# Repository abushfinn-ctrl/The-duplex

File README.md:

# The-duplex
A wireless split keyboard with 42 keys, made in a 3d printed case. Designed and built for HackClub and improved typing erogonomics. I got a new Macbook lately and my old keyboard was on it's last few breaths, so I decided to make a new keyboard that is also ergonomic. You can use the PCB files to order the PCB from Jlcpcb or your preffered PCB manufacturer. The bill of materials is also provided, look at aliexpress but if the parts are available locally for cheaper then obviously that would work aswell. I printed the case in Clay colour Matte PLA with a layer height of 0.2mm on my Prusa Mk3s+.
# Finished!
I finished the project and i've been waiting to be a little bit more free with school to do this journal. I modified the case because it was going to be too thick with the battery inside so I decided to put the battery on top next to the keys. Everything went pretty smoothly I used some heat inserts and double sided tape for the battery. Overall I like it, it looks cool but I'm not sure I really enjoy typing on it. It's not quite the right positions for the keys and it's just off so I can only get 45WPM vs my normal 110WPM. But i learnt a lot and had fun! I added some leather on the bottom so it grips a little better too.

# The Schematic
The schematic is split into a left and right side with the root sheet having the mousebites.
Here is the left side. 

And here is the right side. Exactly the same.

 We can achieve this by using hierarchical sheets. 
 
To make hierarchical sheeting you can click this button on the side bar or the keyboard button S.
Once setup your heirarchy should look like this.

# The PCB
The PCB is fairly simple. Import a template into kicad to use as a layout tool on where to place the switches. I used ergogen (https://ergogen.xyz/new) to edit a layout and then important that into Kicad as an image to get roughly lined up. Here is my PCB at the very end after routing and drawing my edge cuts.

Don't forget to add some customisation like your name!

# The Case 
I designed the case in Autodesk Fusion, there we're 100% some issues but nothing a bit of time and youtube videos can't fix. I designed the top and then bottom then mirrored and copied them for the other side.

# BOM
| Item                        | Description                                  | Quantity | Unit Price (CAD$) | Total Price (CAD$) | Unit Price (USD$) | Total Price (USD$) | URL                                                                                                                                                                                                                                                                                                                                                                                                                                                                                                                                                                                                                                                                                                       | Running total (CAD$ with tax) | Running total (USD$ with tax) |
| --------------------------- | -------------------------------------------- | -------- | ----------------- | ------------------ | ----------------- | ------------------ | --------------------------------------------------------------------------------------------------------------------------------------------------------------------------------------------------------------------------------------------------------------------------------------------------------------------------------------------------------------------------------------------------------------------------------------------------------------------------------------------------------------------------------------------------------------------------------------------------------------------------------------------------------------------------------------------------------- | ----------------------------- | ----------------------------- |
| 102050 1000mAh LiPO Battery | 20mm\*50mm\*10mm 3.7v Lithium battery. 2Pack | 1        | $12.38            | $12.38             | $8.90             | $8.90              | [Battery](https://www.aliexpress.com/item/1005006394926759.html?spm=a2g0o.cart.0.0.717138da7HBbtz&mp=1&pdp_npi=6%40dis%21CAD%21CAD%2020.30%21CAD%2012.38%21%21CAD%2012.38%21%21%21%4021030a6217721181818113051eb8cd%2112000037011657000%21ct%21CA%21-1%21%211%210%21)                                                                                                                                                                                                                                                                                                                                                                                                                                     | 12.38$                        | 8.90$                         |
| Gateron Switches 50 Pack    | 50 Gateron Auburn Switches                   | 1        | $22.71            | $22.71             | $16.33            | $16.33             | [Switches](https://www.aliexpress.com/item/1005006091988869.html?spm=a2g0o.cart.0.0.717138daN9Xo9a&mp=1&pdp_npi=6%40dis%21CAD%21CAD%2022.71%21CAD%2016.50%21%21CAD%2016.50%21%21%21%402103126e17721187661706203ef36d%2112000035698597741%21ct%21CA%21-1%21%211%210%21)                                                                                                                                                                                                                                                                                                                                                                                                                                    | 35.09$                        | 25.23$                        |
| XIAO nRF52840               | XIAO 2 pack microcontroller                  | 1        | $47.72            | $47.72             | $34.31            | $34.31             | [XIAO](https://www.aliexpress.com/item/1005009937098547.html?spm=a2g0o.cart.0.0.717138daN9Xo9a&mp=1&pdp_npi=6%40dis%21CAD%21CAD%2038.79%21CAD%2038.79%21%21CAD%2038.79%21%21%21%402103126e17721187661706203ef36d%2112000053206770722%21ct%21CA%21-1%21%211%210%21)                                                                                                                                                                                                                                                                                                                                                                                                                                        | 82.81$                        | 59.54$                        |
| Gateron Hotswap Sockets     | 70pack of Gateron hotswap sockets            | 1        | $22.64            | $22.64             | $16.28            | $16.28             | [Hotswap Sockets](https://www.aliexpress.com/item/1005007267551458.html?spm=a2g0o.productlist.main.2.6775445alZJMq9&algo_pvid=8333edd5-5946-4213-8dd2-250f714a57a7&algo_exp_id=8333edd5-5946-4213-8dd2-250f714a57a7-1&pdp_ext_f=%7B%22order%22%3A%22116%22%2C%22eval%22%3A%221%22%2C%22fromPage%22%3A%22search%22%7D&pdp_npi=6%40dis%21CAD%2111.03%211.59%21%21%2153.99%217.80%21%402101d6ff17721194373734938ee5ee%2112000040367341585%21sea%21CA%210%21ABX%211%210%21n_tag%3A-29910%3Bd%3Af7fad9c5%3Bm03_new_user%3A-29895%3BpisId%3A5000000197831975&curPageLogUid=QSxKiYfJkGM5&utparam-url=scene%3Asearch%7Cquery_from%3A%7Cx_object_id%3A1005007267551458%7C_p_origin_prod%3A)                        | 105.45$                       | 75.81$                        |
| PCB                         | 5 PCB's ordered from JLCPCB                  | 1        | $58.41            | $58.41             | $41.99            | $41.99             | N/A                                                                                                                                                                                                                                                                                                                                                                                                                                                                                                                                                                                                                                                                                                       | 163.86$                       | 117.81$                       |
| 1N5189 Diodes               | 100 pieces                                   | 1        | $3.05             | $3.05              | $2.19             | $2.19              | [DIODE](https://www.aliexpress.com/item/1005004617332808.html?spm=a2g0o.productlist.main.2.6d095c7c8zgvdj&algo_pvid=a741c6a4-8f37-4fc7-9e49-6e10b294d7f1&algo_exp_id=a741c6a4-8f37-4fc7-9e49-6e10b294d7f1-1&pdp_ext_f=%7B%22order%22%3A%2227%22%2C%22spu_best_type%22%3A%22price%22%2C%22eval%22%3A%221%22%2C%22fromPage%22%3A%22search%22%7D&pdp_npi=6%40dis%21CAD%213.05%211.59%21%21%212.19%211.14%21%402101e2b417736070752314599edabc%2112000029848432899%21sea%21CA%210%21ABX%211%210%21n_tag%3A-29910%3Bd%3A893a898a%3Bm03_new_user%3A-29895%3BpisId%3A5000000197831859&curPageLogUid=KM5DeZYwbAHX&utparam-url=scene%3Asearch%7Cquery_from%3A%7Cx_object_id%3A1005004617332808%7C_p_origin_prod%3A) | 166.91$                       | 120.00$                       |
| Keycaps                     | Already have                                 |          |                   |                    |                   |                    |                                                                                                                                                                                                                                                                                                                                                                                                                                                                                                                                                                                                                                                                                                           |                               |                               |

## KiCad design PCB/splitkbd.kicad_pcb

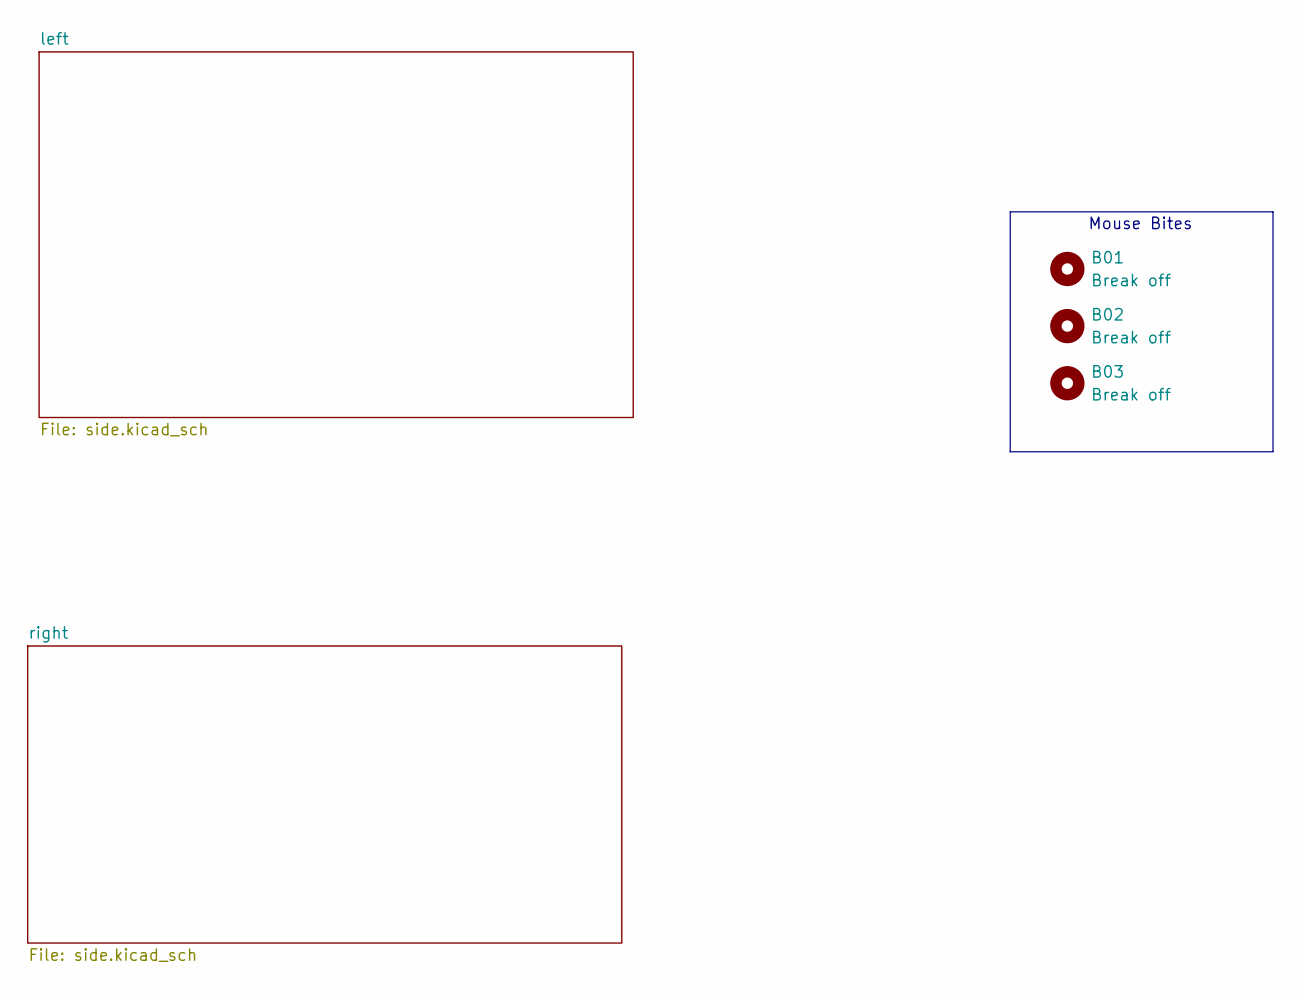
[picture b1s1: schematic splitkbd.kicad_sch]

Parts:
B01, B02, B03: Break off; mouse-bite-5mm-slot

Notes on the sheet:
Mouse Bites

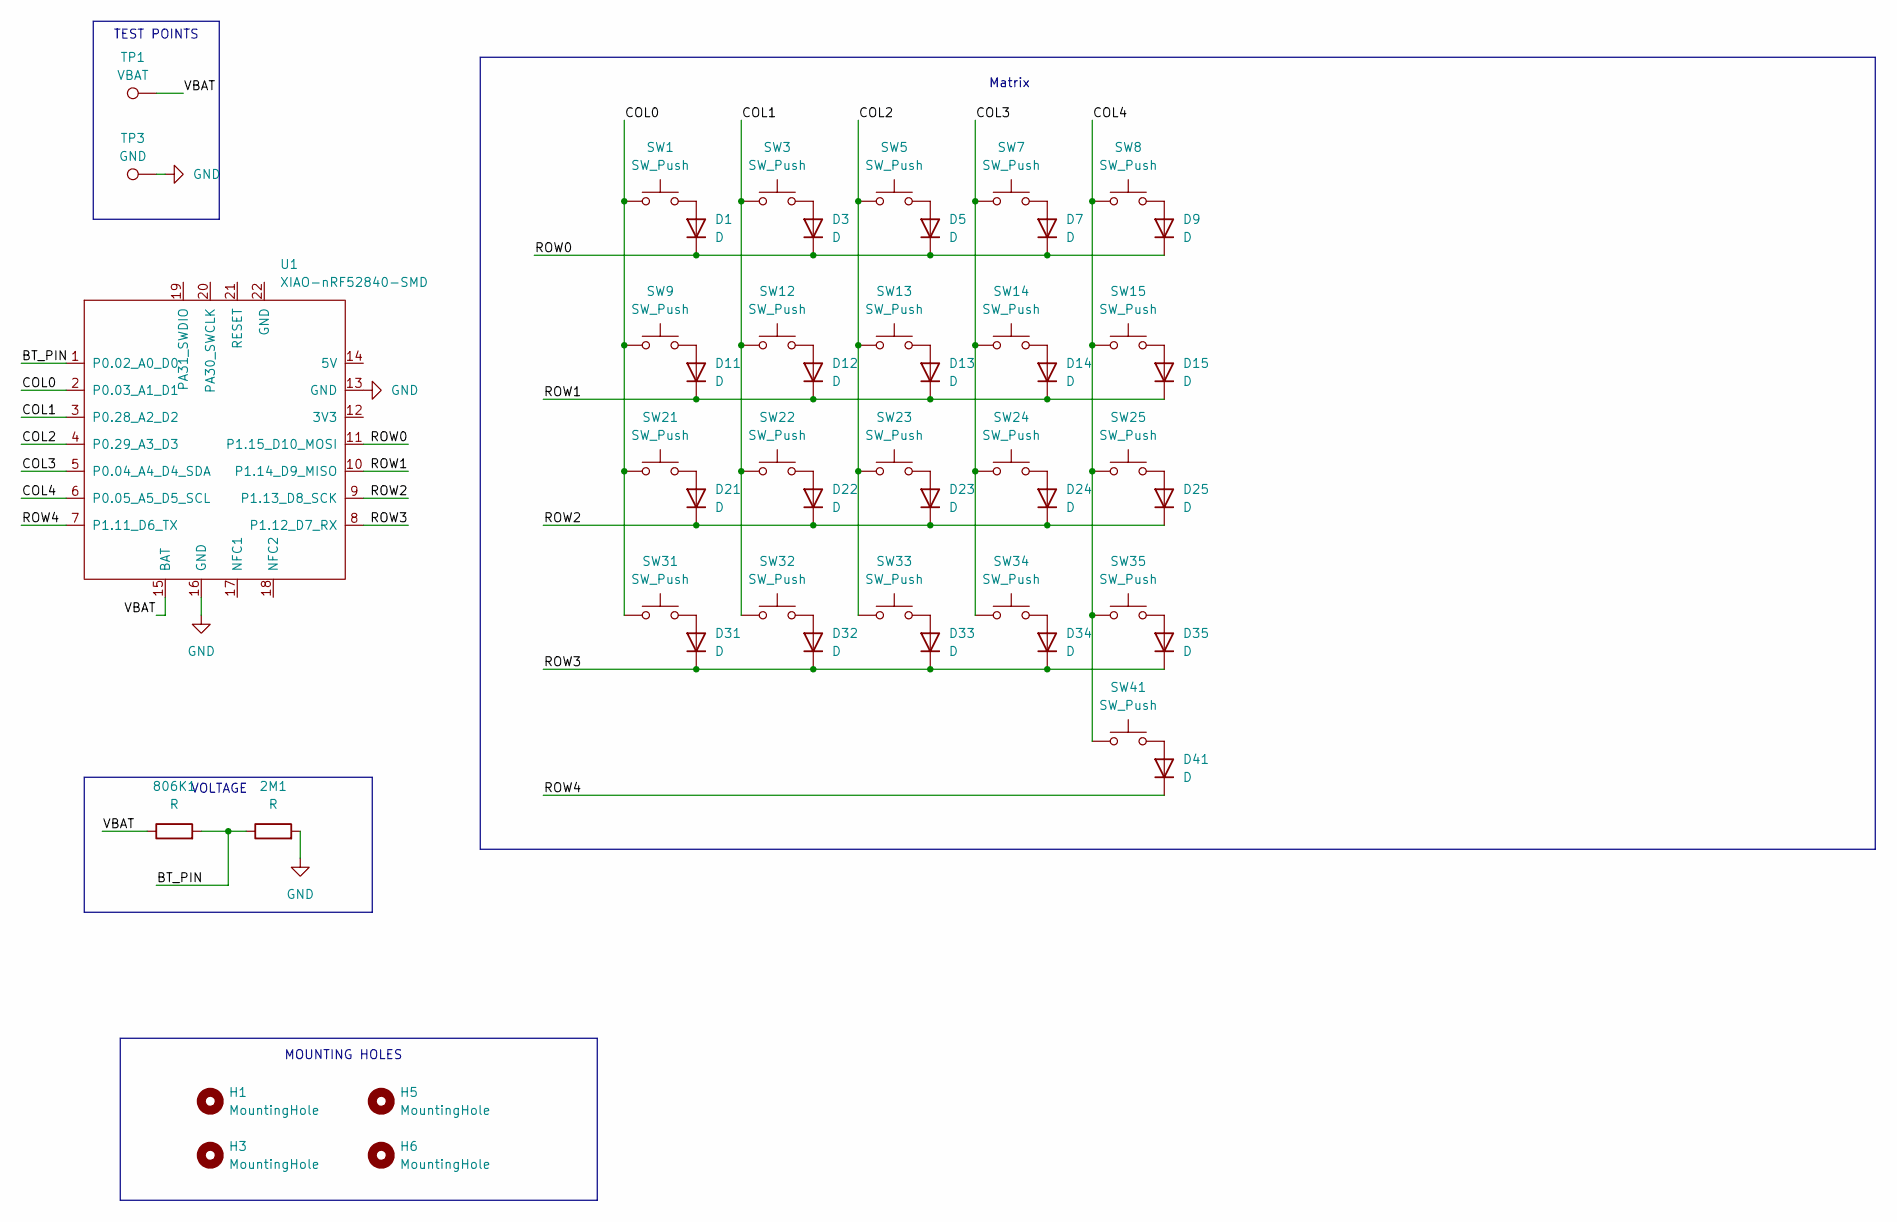
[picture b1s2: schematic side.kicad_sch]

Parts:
2M1, 806K1: R; R_0805_2012Metric
D1, D3, D5, D7, D9, D11, D12, D13, D14, D15, D21, D22, D23, D24, D25, D31, D32, D33, D34, D35, D41: D; D_SOD-123
H1, H3, H5, H6: MountingHole; MountingHole_3.2mm_M3
SW1, SW3, SW5, SW7, SW8, SW9, SW12, SW13, SW14, SW15, SW21, SW22, SW23, SW24, SW25, SW31, SW32, SW33, SW34, SW35, SW41: SW_Push; SW_MX_HS_CPG151101S11_1.25u
TP1: VBAT; TestPoint_Pad_2.0x2.0mm
TP3: GND; TestPoint_Pad_2.0x2.0mm
U1: XIAO-nRF52840-SMD; modified-XIAO-nRF52840-SMD

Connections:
/left/BT_PIN: 2M1.1, 806K1.2, U1.1 (P0.02_A0_D0)
/left/COL0: SW1.1, SW9.1, SW21.1, SW31.1, U1.2 (P0.03_A1_D1)
/left/COL1: SW3.1, SW12.1, SW22.1, SW32.1, U1.3 (P0.28_A2_D2)
/left/COL2: SW5.1, SW13.1, SW23.1, SW33.1, U1.4 (P0.29_A3_D3)
/left/COL3: SW7.1, SW14.1, SW24.1, SW34.1, U1.5 (P0.04_A4_D4_SDA)
/left/COL4: SW8.1, SW15.1, SW25.1, SW35.1, SW41.1, U1.6 (P0.05_A5_D5_SCL)
/left/ROW0: D1.1 (K), D3.1 (K), D5.1 (K), D7.1 (K), D9.1 (K), U1.11 (P1.15_D10_MOSI)
/left/ROW1: D11.1 (K), D12.1 (K), D13.1 (K), D14.1 (K), D15.1 (K), U1.10 (P1.14_D9_MISO)
/left/ROW2: D21.1 (K), D22.1 (K), D23.1 (K), D24.1 (K), D25.1 (K), U1.9 (P1.13_D8_SCK)
/left/ROW3: D31.1 (K), D32.1 (K), D33.1 (K), D34.1 (K), D35.1 (K), U1.8 (P1.12_D7_RX)
/left/ROW4: D41.1 (K), U1.7 (P1.11_D6_TX)
/left/VBAT: 806K1.1, TP1.1, U1.15 (BAT)
GND: 2M1.2, TP3.1, U1.13 (GND), U1.16 (GND); also elsewhere on the board
unnamed: D1.2 (A), SW1.2
unnamed: D3.2 (A), SW3.2
unnamed: D5.2 (A), SW5.2
unnamed: D7.2 (A), SW7.2
unnamed: D9.2 (A), SW8.2
unnamed: D11.2 (A), SW9.2
unnamed: D12.2 (A), SW12.2
unnamed: D13.2 (A), SW13.2
unnamed: D14.2 (A), SW14.2
unnamed: D15.2 (A), SW15.2
unnamed: D21.2 (A), SW21.2
unnamed: D22.2 (A), SW22.2
unnamed: D23.2 (A), SW23.2
unnamed: D24.2 (A), SW24.2
unnamed: D25.2 (A), SW25.2
unnamed: D31.2 (A), SW31.2
unnamed: D32.2 (A), SW32.2
unnamed: D33.2 (A), SW33.2
unnamed: D34.2 (A), SW34.2
unnamed: D35.2 (A), SW35.2
unnamed: D41.2 (A), SW41.2

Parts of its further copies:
D2, D4, D6, D8, D10, D16, D17, D18, D19, D20, D26, D27, D28, D29, D30, D36, D37, D38, D39, D40, D42: D; D_SOD-123
H2, H4, H7, H8: MountingHole; MountingHole_3.2mm_M3
R2, R4: R; R_0805_2012Metric
SW2, SW4, SW6, SW10, SW11, SW16, SW17, SW18, SW19, SW20, SW26, SW27, SW28, SW29, SW30, SW36, SW37, SW38, SW39, SW40, SW42: SW_Push; SW_MX_HS_CPG151101S11_1.25u
TP2: VBAT; TestPoint_Pad_2.0x2.0mm
TP4: GND; TestPoint_Pad_2.0x2.0mm
U2: XIAO-nRF52840-SMD; modified-XIAO-nRF52840-SMD

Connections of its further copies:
/right/BT_PIN: R2.2, R4.1, U2.1 (P0.02_A0_D0)
/right/COL0: SW2.1, SW16.1, SW26.1, SW36.1, U2.2 (P0.03_A1_D1)
/right/COL1: SW4.1, SW17.1, SW27.1, SW37.1, U2.3 (P0.28_A2_D2)
/right/COL2: SW6.1, SW18.1, SW28.1, SW38.1, U2.4 (P0.29_A3_D3)
/right/COL3: SW10.1, SW19.1, SW29.1, SW39.1, U2.5 (P0.04_A4_D4_SDA)
/right/COL4: SW11.1, SW20.1, SW30.1, SW40.1, SW42.1, U2.6 (P0.05_A5_D5_SCL)
/right/ROW0: D2.1 (K), D4.1 (K), D6.1 (K), D8.1 (K), D10.1 (K), U2.11 (P1.15_D10_MOSI)
/right/ROW1: D16.1 (K), D17.1 (K), D18.1 (K), D19.1 (K), D20.1 (K), U2.10 (P1.14_D9_MISO)
/right/ROW2: D26.1 (K), D27.1 (K), D28.1 (K), D29.1 (K), D30.1 (K), U2.9 (P1.13_D8_SCK)
/right/ROW3: D36.1 (K), D37.1 (K), D38.1 (K), D39.1 (K), D40.1 (K), U2.8 (P1.12_D7_RX)
/right/ROW4: D42.1 (K), U2.7 (P1.11_D6_TX)
/right/VBAT: R2.1, TP2.1, U2.15 (BAT)
GND: R4.2, TP4.1, U2.13 (GND), U2.16 (GND); also elsewhere on the board
unnamed: D2.2 (A), SW2.2
unnamed: D4.2 (A), SW4.2
unnamed: D6.2 (A), SW6.2
unnamed: D8.2 (A), SW10.2
unnamed: D10.2 (A), SW11.2
unnamed: D16.2 (A), SW16.2
unnamed: D17.2 (A), SW17.2
unnamed: D18.2 (A), SW18.2
unnamed: D19.2 (A), SW19.2
unnamed: D20.2 (A), SW20.2
unnamed: D26.2 (A), SW26.2
unnamed: D27.2 (A), SW27.2
unnamed: D28.2 (A), SW28.2
unnamed: D29.2 (A), SW29.2
unnamed: D30.2 (A), SW30.2
unnamed: D36.2 (A), SW36.2
unnamed: D37.2 (A), SW37.2
unnamed: D38.2 (A), SW38.2
unnamed: D39.2 (A), SW39.2
unnamed: D40.2 (A), SW40.2
unnamed: D42.2 (A), SW42.2

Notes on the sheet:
VOLTAGE
MOUNTING HOLES
TEST POINTS
Matrix

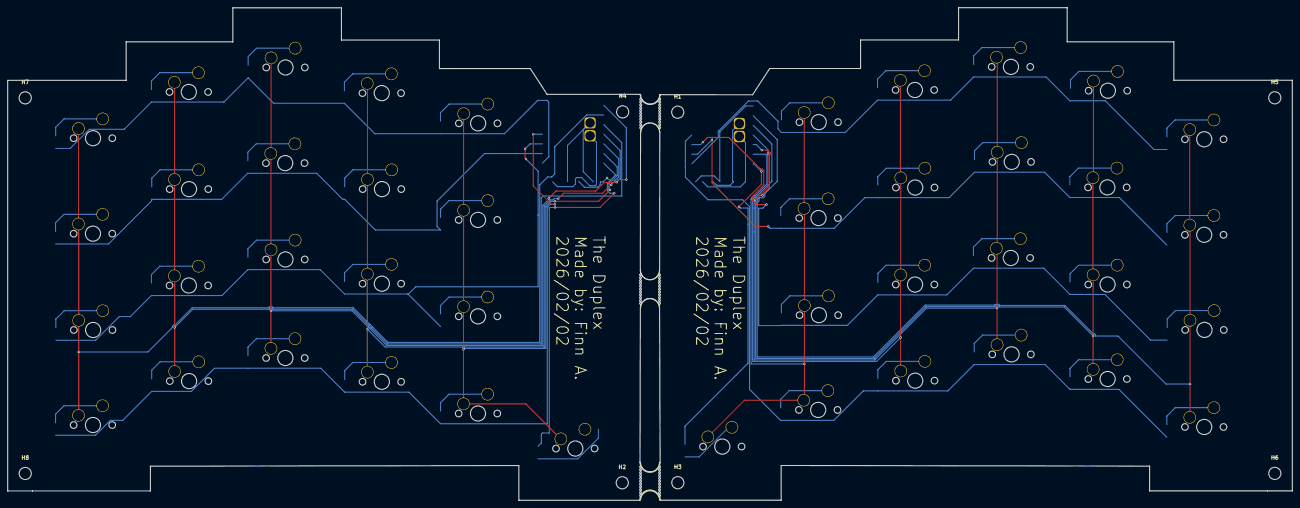
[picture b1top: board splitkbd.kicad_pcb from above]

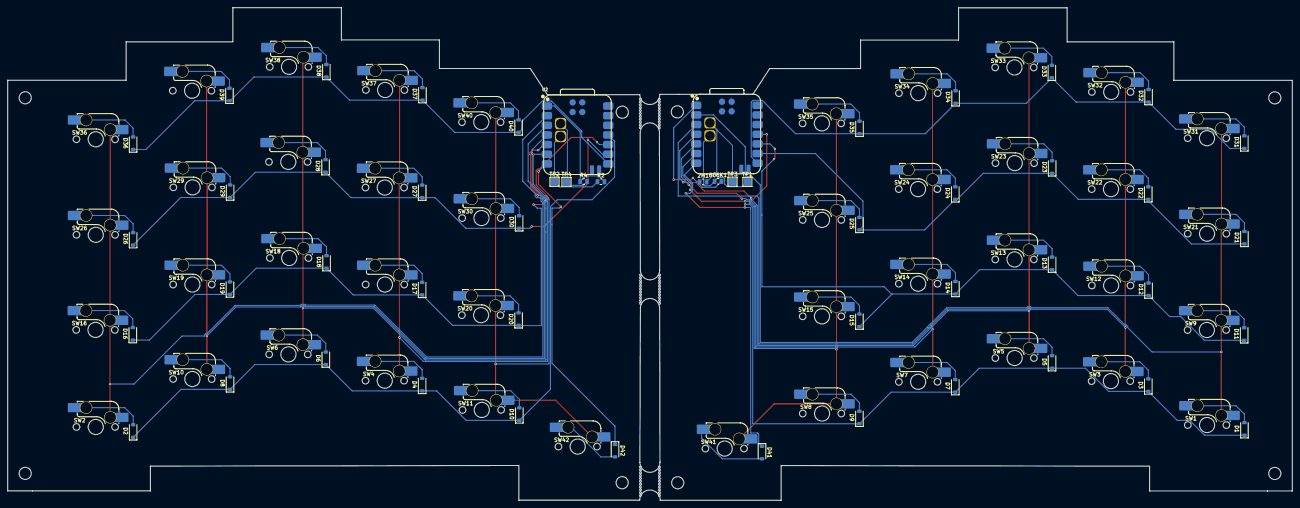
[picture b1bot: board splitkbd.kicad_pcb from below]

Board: 2 copper layers, 338.3 x 129.7 mm, 105 parts (94 on the bottom side), 67 nets.
